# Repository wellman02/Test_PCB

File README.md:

# TEST KiCad
 Testowe PCB numpada zrobionego w KiCadzie

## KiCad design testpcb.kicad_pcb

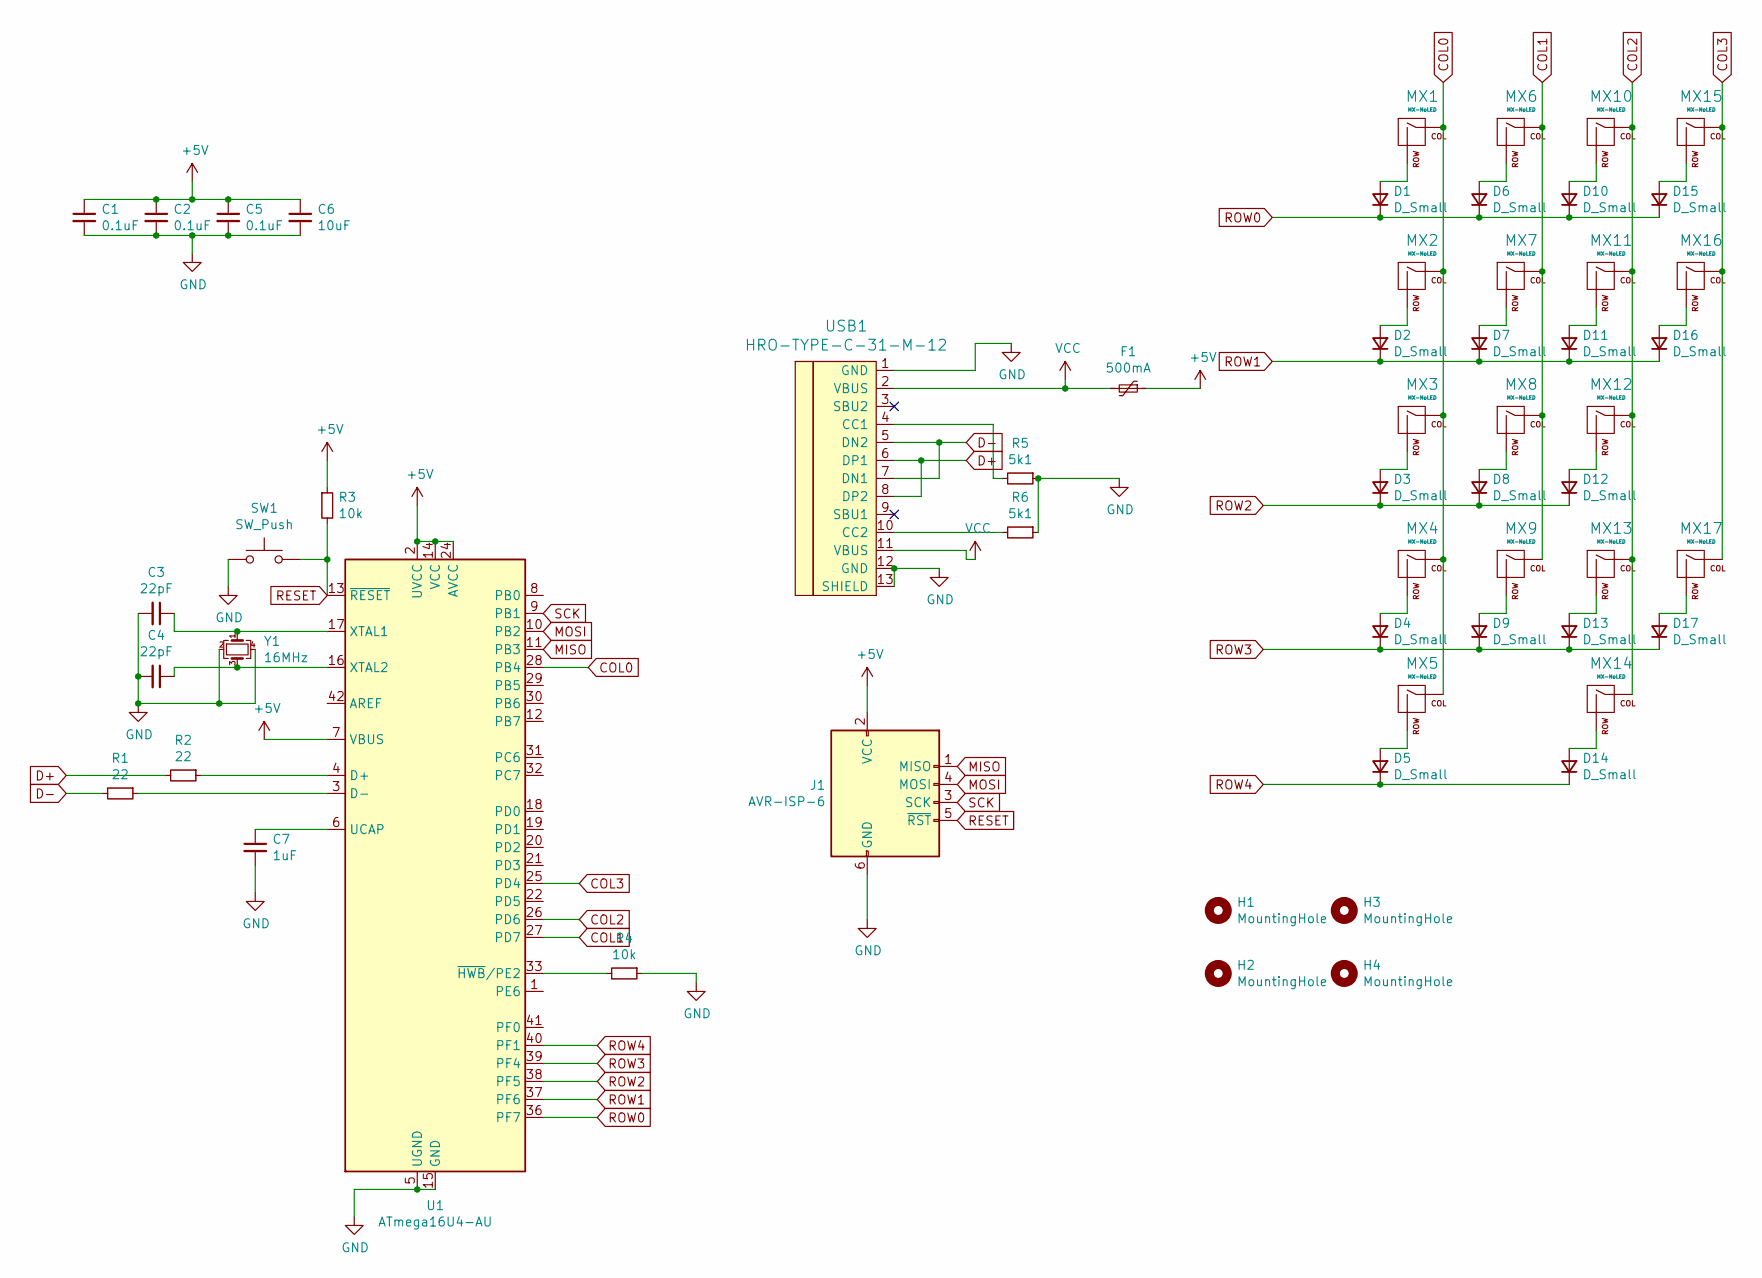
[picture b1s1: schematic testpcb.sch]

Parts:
C1, C2, C5: 0.1uF; C_0805_2012Metric
C3, C4: 22pF; C_0805_2012Metric
C6: 10uF; C_0805_2012Metric
C7: 1uF; C_0805_2012Metric
D1, D2, D3, D4, D5, D6, D7, D8, D9, D10, D11, D12, D13, D14, D15, D16, D17: D_Small; D_SOD-123
F1: 500mA; Fuse_1206_3216Metric
H1, H2, H3, H4: MountingHole; MountingHole_2.1mm
J1: AVR-ISP-6; Reset_Pretty-Mask
MX1, MX2, MX3, MX4, MX6, MX7, MX8, MX9, MX10, MX11, MX12, MX13, MX14, MX15: MX-NoLED; MXOnly-1U
MX5, MX16, MX17: MX-NoLED; MXOnly-2U
R1, R2: 22; R_0805_2012Metric
R3, R4: 10k; R_0805_2012Metric
R5, R6: 5k1; R_0805_2012Metric
SW1: SW_Push; SKQG-1155865
U1: ATmega16U4-AU; TQFP-44_10x10mm_P0.8mm
USB1: HRO-TYPE-C-31-M-12; HRO-TYPE-C-31-M-12-Assembly
Y1: 16MHz; Crystal_SMD_3225-4Pin_3.2x2.5mm

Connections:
+5V: C1.1, C2.1, C5.1, C6.1, F1.1, J1.2 (VCC), R3.1, U1.2 (UVCC), U1.7 (VBUS), U1.14 (VCC), U1.24 (AVCC), U1.34 (VCC), U1.44 (AVCC)
COL0: MX1.1 (COL), MX2.1 (COL), MX3.1 (COL), MX4.1 (COL), MX5.1 (COL), U1.28 (PB4)
COL1: MX6.1 (COL), MX7.1 (COL), MX8.1 (COL), MX9.1 (COL), U1.27 (PD7)
COL2: MX10.1 (COL), MX11.1 (COL), MX12.1 (COL), MX13.1 (COL), MX14.1 (COL), U1.26 (PD6)
COL3: MX15.1 (COL), MX16.1 (COL), MX17.1 (COL), U1.25 (PD4)
D+: R2.2, USB1.6 (DP1), USB1.8 (DP2)
D-: R1.2, USB1.5 (DN2), USB1.7 (DN1)
GND: C1.2, C2.2, C3.2, C4.2, C5.2, C6.2, C7.2, J1.6 (GND), R4.1, R5.1, R6.1, SW1.1, U1.5 (UGND), U1.15 (GND), U1.23 (GND), U1.35 (GND), U1.43 (GND), USB1.1 (GND), USB1.12 (GND), USB1.13 (SHIELD), Y1.2, Y1.4
MISO: J1.1 (MISO), U1.11 (PB3)
MOSI: J1.4 (MOSI), U1.10 (PB2)
unnamed: C3.1, U1.17 (XTAL1), Y1.1
unnamed: C4.1, U1.16 (XTAL2), Y1.3
unnamed: C7.1, U1.6 (UCAP)
unnamed: D1.2 (A), MX1.2 (ROW)
unnamed: D2.2 (A), MX2.2 (ROW)
unnamed: D3.2 (A), MX3.2 (ROW)
unnamed: D4.2 (A), MX4.2 (ROW)
unnamed: D5.2 (A), MX5.2 (ROW)
unnamed: D6.2 (A), MX6.2 (ROW)
unnamed: D7.2 (A), MX7.2 (ROW)
unnamed: D8.2 (A), MX8.2 (ROW)
unnamed: D9.2 (A), MX9.2 (ROW)
unnamed: D10.2 (A), MX10.2 (ROW)
unnamed: D11.2 (A), MX11.2 (ROW)
unnamed: D12.2 (A), MX12.2 (ROW)
unnamed: D13.2 (A), MX13.2 (ROW)
unnamed: D14.2 (A), MX14.2 (ROW)
unnamed: D15.2 (A), MX15.2 (ROW)
unnamed: D16.2 (A), MX16.2 (ROW)
unnamed: D17.2 (A), MX17.2 (ROW)
unnamed: R1.1, U1.3 (D-)
unnamed: R2.1, U1.4 (D+)
unnamed: R4.2, U1.33 (~HWB~/PE2)
unnamed: R5.2, USB1.4 (CC1)
unnamed: R6.2, USB1.10 (CC2)
RESET: J1.5 (~RST), R3.2, SW1.2, U1.13 (~RESET)
ROW0: D1.1 (K), D6.1 (K), D10.1 (K), D15.1 (K), U1.36 (PF7)
ROW1: D2.1 (K), D7.1 (K), D11.1 (K), D16.1 (K), U1.37 (PF6)
ROW2: D3.1 (K), D8.1 (K), D12.1 (K), U1.38 (PF5)
ROW3: D4.1 (K), D9.1 (K), D13.1 (K), D17.1 (K), U1.39 (PF4)
ROW4: D5.1 (K), D14.1 (K), U1.40 (PF1)
SCK: J1.3 (SCK), U1.9 (PB1)
VCC: F1.2, USB1.2 (VBUS), USB1.11 (VBUS)

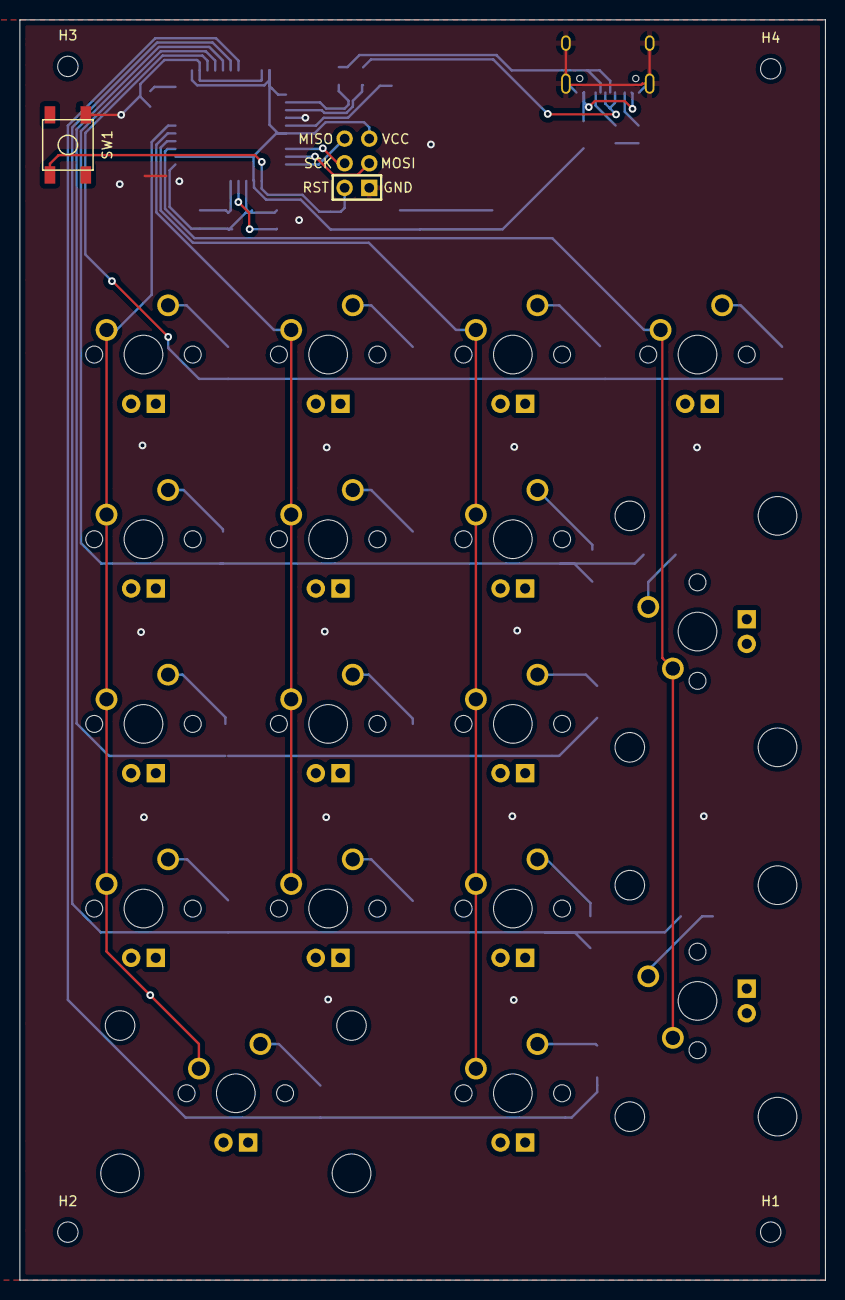
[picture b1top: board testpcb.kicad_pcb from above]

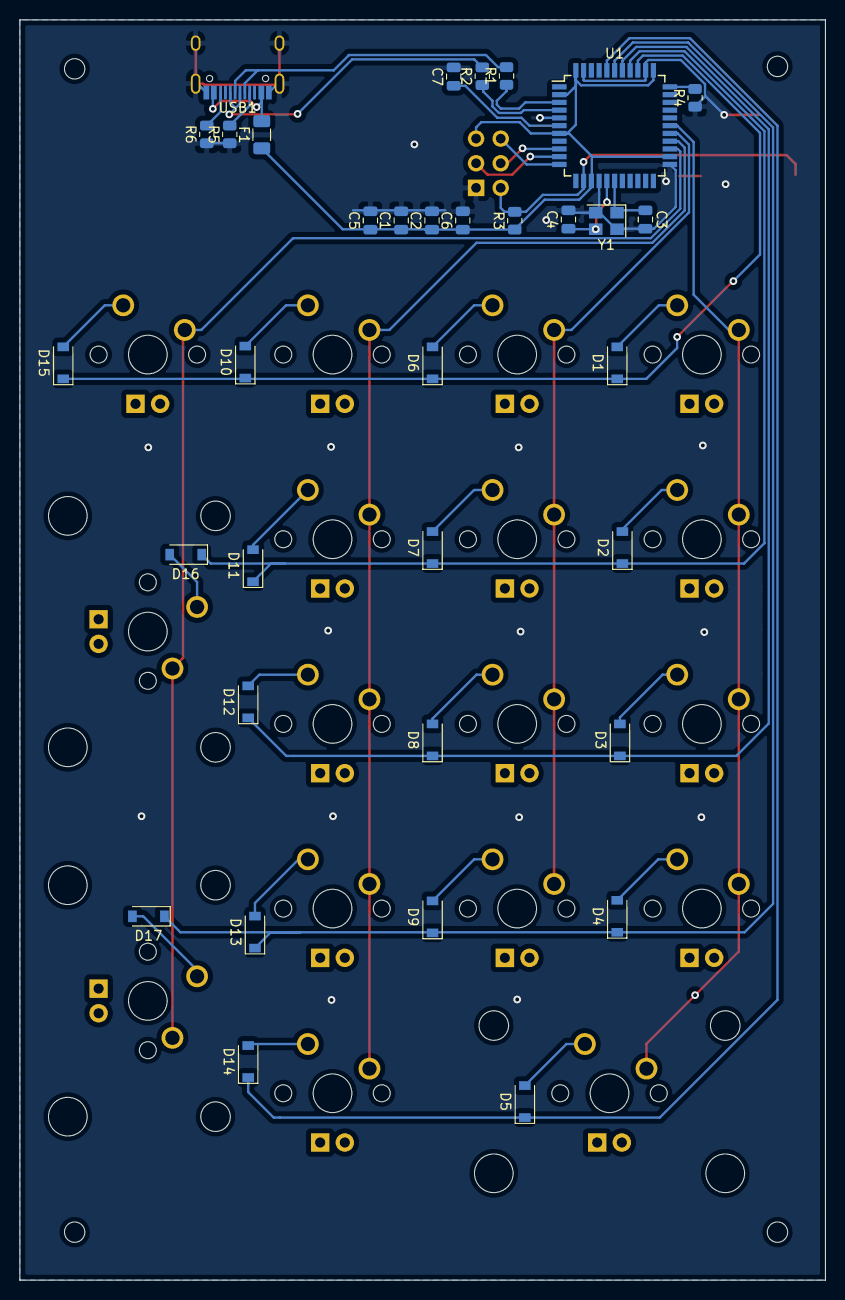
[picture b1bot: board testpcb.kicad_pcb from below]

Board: 2 copper layers, 83.1 x 130.0 mm, 57 parts (34 on the bottom side), 43 nets.

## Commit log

2021-05-24 inicjalizacja
2021-05-24 biblioteki load
2021-05-24 MCU Schematic done
2021-05-25 pady poustawiane
2021-05-25 ulozenie git
2021-05-25 DONE
2021-05-25 jakies poprawki chyba
2021-05-26 jakies poprawki kolejne
2021-05-27 polaczone switche / wizualne poprawki tracerow
2021-05-27 gowno
2021-05-27 naprawione coppery
2021-05-28 poprawki
2021-05-30 mounting holes
